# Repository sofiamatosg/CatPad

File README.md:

# CatPad
Repository for my Hackpad

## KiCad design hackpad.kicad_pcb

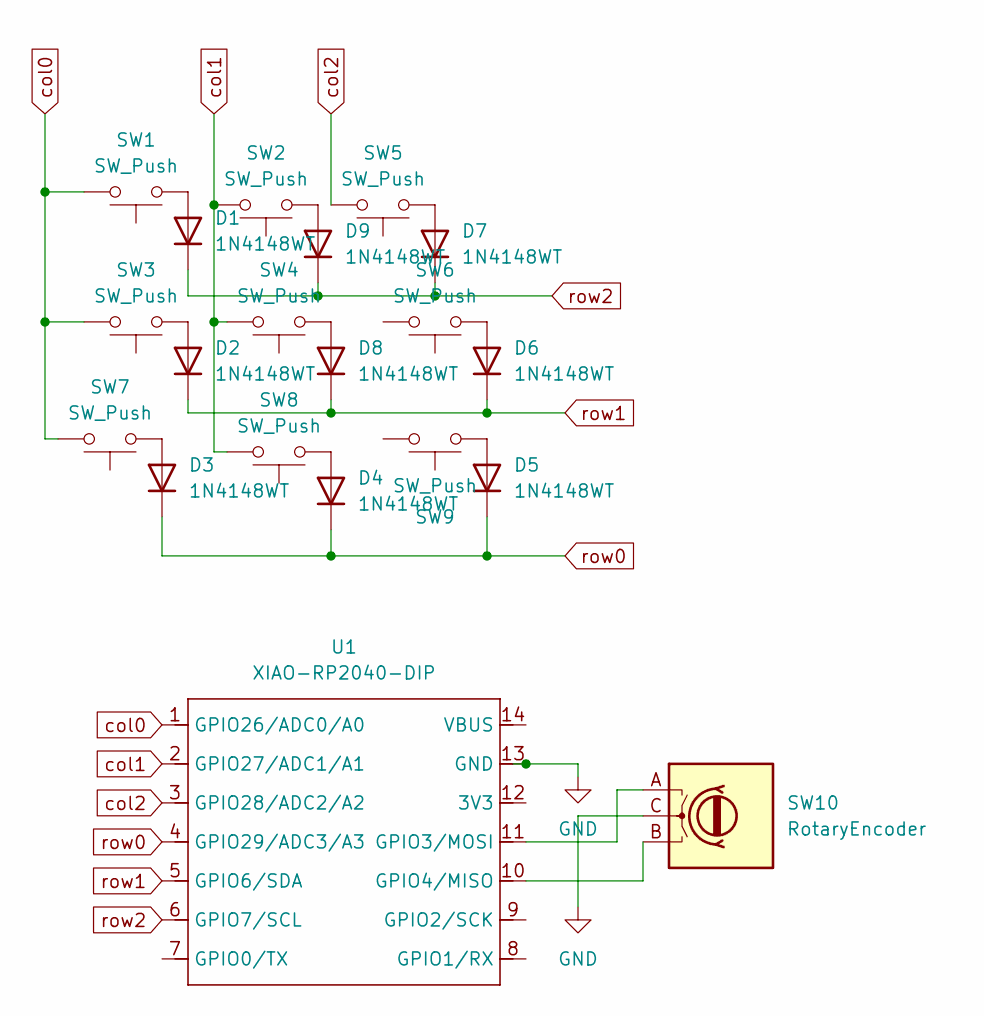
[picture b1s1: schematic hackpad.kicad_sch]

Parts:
D1, D2, D3, D4, D5, D6, D7, D8, D9: 1N4148WT; D_DO-35_SOD27_P2.54mm_Vertical_AnodeUp
SW1, SW2, SW3, SW4, SW5, SW6, SW7, SW8, SW9: SW_Push; SW_Cherry_MX_1.00u_PCB
SW10: RotaryEncoder; RotaryEncoder_Alps_EC12E-Switch_Vertical_H20mm_CircularMoun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
U1: XIAO-RP2040-DIP; MOUDLE14P-XIAO-DIP-SMD

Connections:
GND: SW10.C, U1.13 (GND)
unnamed: D1.2 (A), SW1.1
unnamed: D2.2 (A), SW3.1
unnamed: D3.2 (A), SW7.1
unnamed: D4.2 (A), SW8.1
unnamed: D5.2 (A), SW9.1
unnamed: D6.2 (A), SW6.1
unnamed: D7.2 (A), SW5.1
unnamed: D8.2 (A), SW4.1
unnamed: D9.2 (A), SW2.1
unnamed: SW10.A, U1.11 (GPIO3/MOSI)
unnamed: SW10.B, U1.10 (GPIO4/MISO)
col0: SW1.2, SW3.2, SW7.2, U1.1 (GPIO26/ADC0/A0)
col1: SW2.2, SW4.2, SW8.2, U1.2 (GPIO27/ADC1/A1)
col2: SW5.2, U1.3 (GPIO28/ADC2/A2)
row0: D3.1 (K), D4.1 (K), D5.1 (K), U1.4 (GPIO29/ADC3/A3)
row1: D2.1 (K), D6.1 (K), D8.1 (K), U1.5 (GPIO6/SDA)
row2: D1.1 (K), D7.1 (K), D9.1 (K), U1.6 (GPIO7/SCL)

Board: 2 copper layers, 19 parts (0 on the bottom side), 14 nets, no tracks yet.

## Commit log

2025-06-24 Start of hackpad
